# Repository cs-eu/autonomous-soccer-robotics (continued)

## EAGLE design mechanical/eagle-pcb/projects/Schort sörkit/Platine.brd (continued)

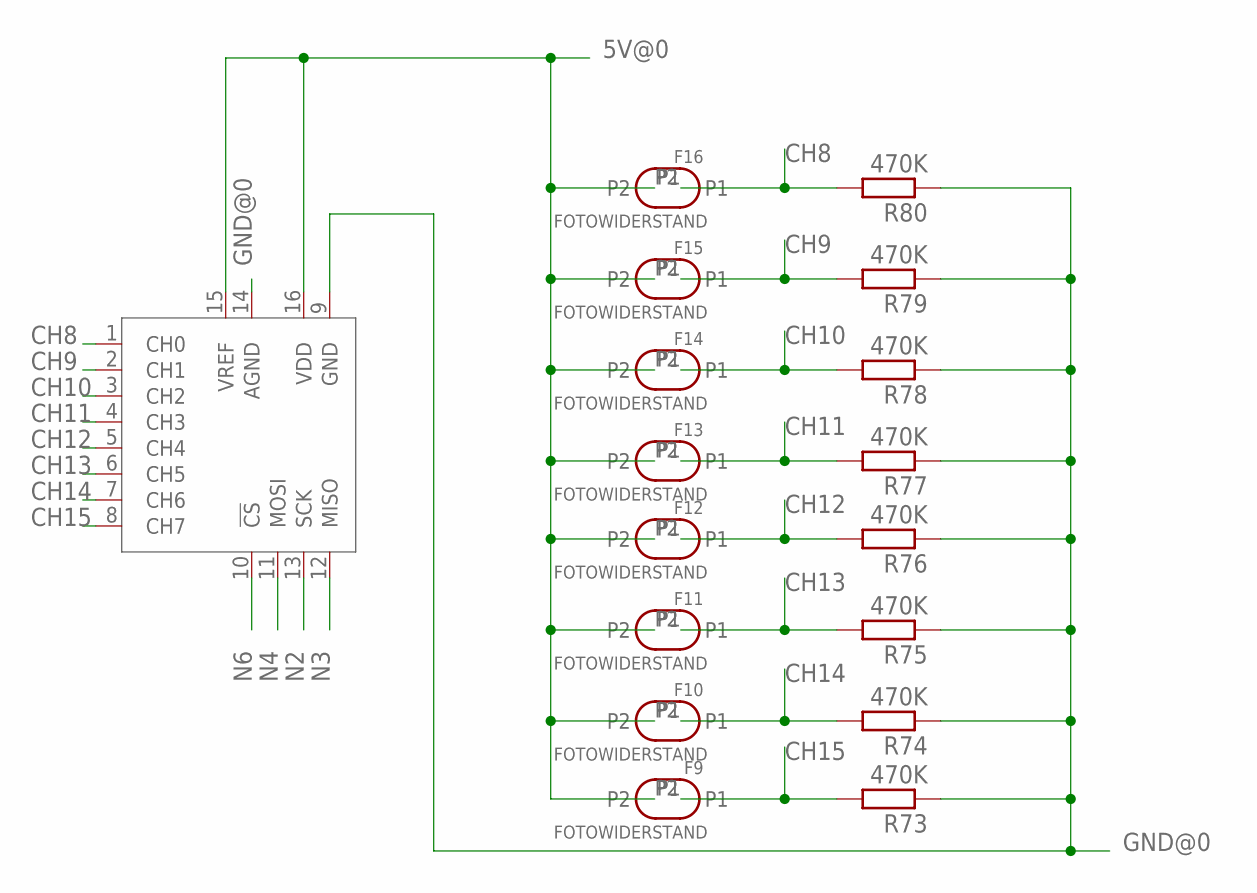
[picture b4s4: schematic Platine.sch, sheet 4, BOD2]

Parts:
F9, F10, F11, F12, F13, F14, F15, F16: FOTOWIDERSTAND
R73, R74, R75, R76, R77, R78, R79, R80: 470K; 0207/7
U$7: MCP3008P; DIL16

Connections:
5V@0: F9.P2, F10.P2, F11.P2, F12.P2, F13.P2, F14.P2, F15.P2, F16.P2, U$7.15 (VREF), U$7.16 (VDD); also elsewhere on the board
CH8: F16.P1, R80.2, U$7.1 (CH0)
CH9: F15.P1, R79.2, U$7.2 (CH1)
CH10: F14.P1, R78.2, U$7.3 (CH2)
CH11: F13.P1, R77.2, U$7.4 (CH3)
CH12: F12.P1, R76.2, U$7.5 (CH4)
CH13: F11.P1, R75.2, U$7.6 (CH5)
CH14: F10.P1, R74.2, U$7.7 (CH6)
CH15: F9.P1, R73.2, U$7.8 (CH7)
GND@0: R73.1, R74.1, R75.1, R76.1, R77.1, R78.1, R79.1, R80.1, U$7.9 (GND), U$7.14 (AGND); also elsewhere on the board
N2: U$7.13 (SCK); also elsewhere on the board
N3: U$7.12 (MISO); also elsewhere on the board
N4: U$7.11 (MOSI); also elsewhere on the board
N6: U$7.10 (!CS); also elsewhere on the board

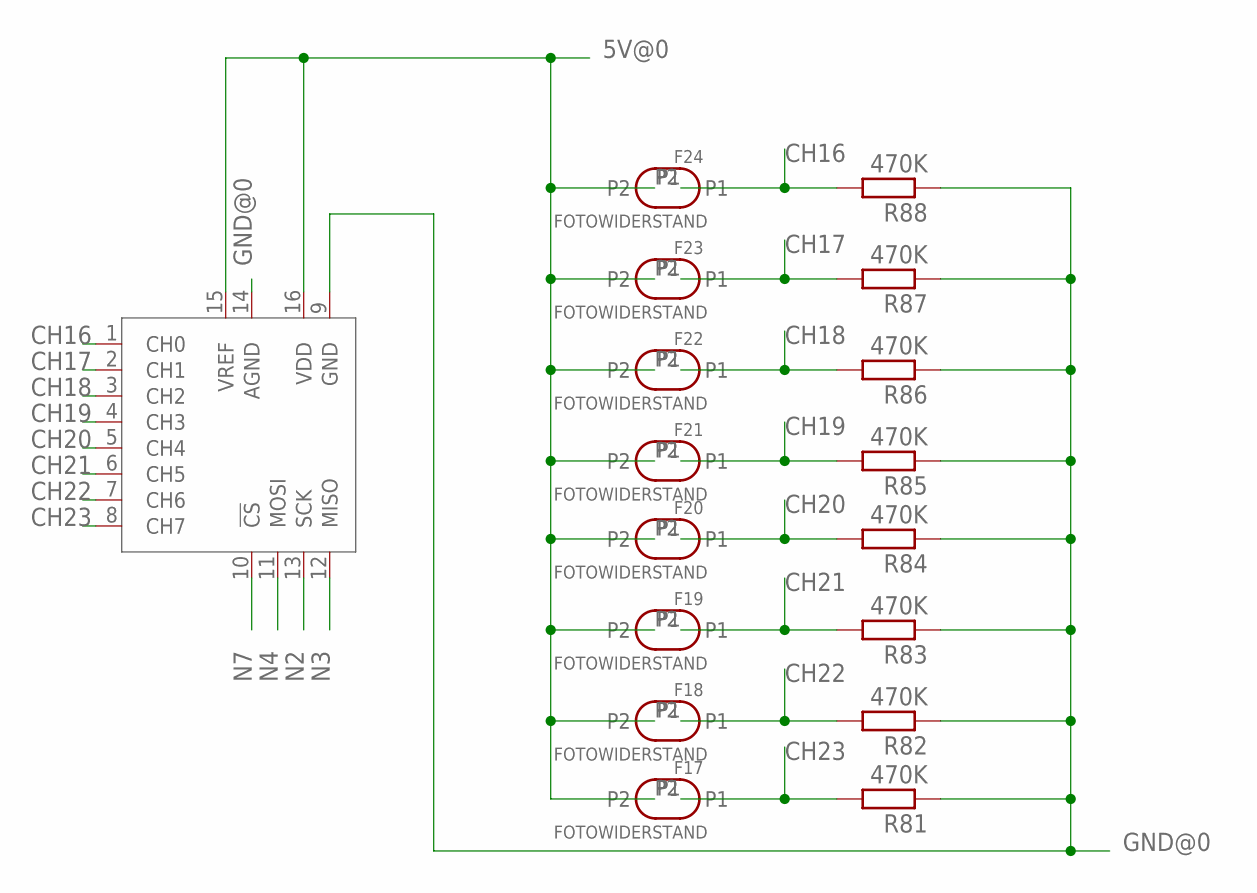
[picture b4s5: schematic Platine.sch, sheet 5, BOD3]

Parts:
F17, F18, F19, F20, F21, F22, F23, F24: FOTOWIDERSTAND
R81, R82, R83, R84, R85, R86, R87, R88: 470K; 0207/7
U$8: MCP3008P; DIL16

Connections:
5V@0: F17.P2, F18.P2, F19.P2, F20.P2, F21.P2, F22.P2, F23.P2, F24.P2, U$8.15 (VREF), U$8.16 (VDD); also elsewhere on the board
CH16: F24.P1, R88.2, U$8.1 (CH0)
CH17: F23.P1, R87.2, U$8.2 (CH1)
CH18: F22.P1, R86.2, U$8.3 (CH2)
CH19: F21.P1, R85.2, U$8.4 (CH3)
CH20: F20.P1, R84.2, U$8.5 (CH4)
CH21: F19.P1, R83.2, U$8.6 (CH5)
CH22: F18.P1, R82.2, U$8.7 (CH6)
CH23: F17.P1, R81.2, U$8.8 (CH7)
GND@0: R81.1, R82.1, R83.1, R84.1, R85.1, R86.1, R87.1, R88.1, U$8.9 (GND), U$8.14 (AGND); also elsewhere on the board
N2: U$8.13 (SCK); also elsewhere on the board
N3: U$8.12 (MISO); also elsewhere on the board
N4: U$8.11 (MOSI); also elsewhere on the board
N7: U$8.10 (!CS); also elsewhere on the board

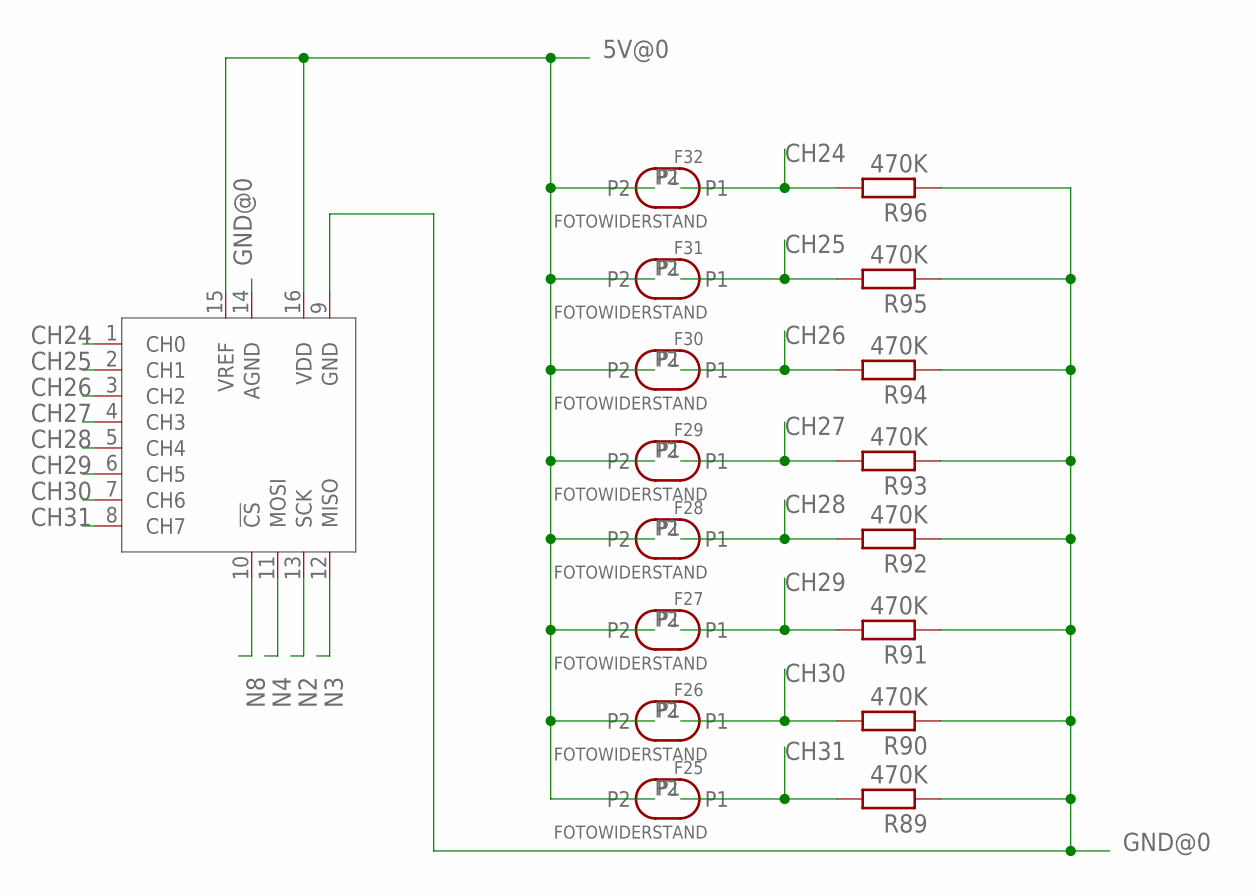
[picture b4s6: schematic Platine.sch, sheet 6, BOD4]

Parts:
F25, F26, F27, F28, F29, F30, F31, F32: FOTOWIDERSTAND
R89, R90, R91, R92, R93, R94, R95, R96: 470K; 0207/7
U$10: MCP3008P; DIL16

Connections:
5V@0: F25.P2, F26.P2, F27.P2, F28.P2, F29.P2, F30.P2, F31.P2, F32.P2, U$10.15 (VREF), U$10.16 (VDD); also elsewhere on the board
CH24: F32.P1, R96.2, U$10.1 (CH0)
CH25: F31.P1, R95.2, U$10.2 (CH1)
CH26: F30.P1, R94.2, U$10.3 (CH2)
CH27: F29.P1, R93.2, U$10.4 (CH3)
CH28: F28.P1, R92.2, U$10.5 (CH4)
CH29: F27.P1, R91.2, U$10.6 (CH5)
CH30: F26.P1, R90.2, U$10.7 (CH6)
CH31: F25.P1, R89.2, U$10.8 (CH7)
GND@0: R89.1, R90.1, R91.1, R92.1, R93.1, R94.1, R95.1, R96.1, U$10.9 (GND), U$10.14 (AGND); also elsewhere on the board
N2: U$10.13 (SCK); also elsewhere on the board
N3: U$10.12 (MISO); also elsewhere on the board
N4: U$10.11 (MOSI); also elsewhere on the board
N8: U$10.10 (!CS); also elsewhere on the board

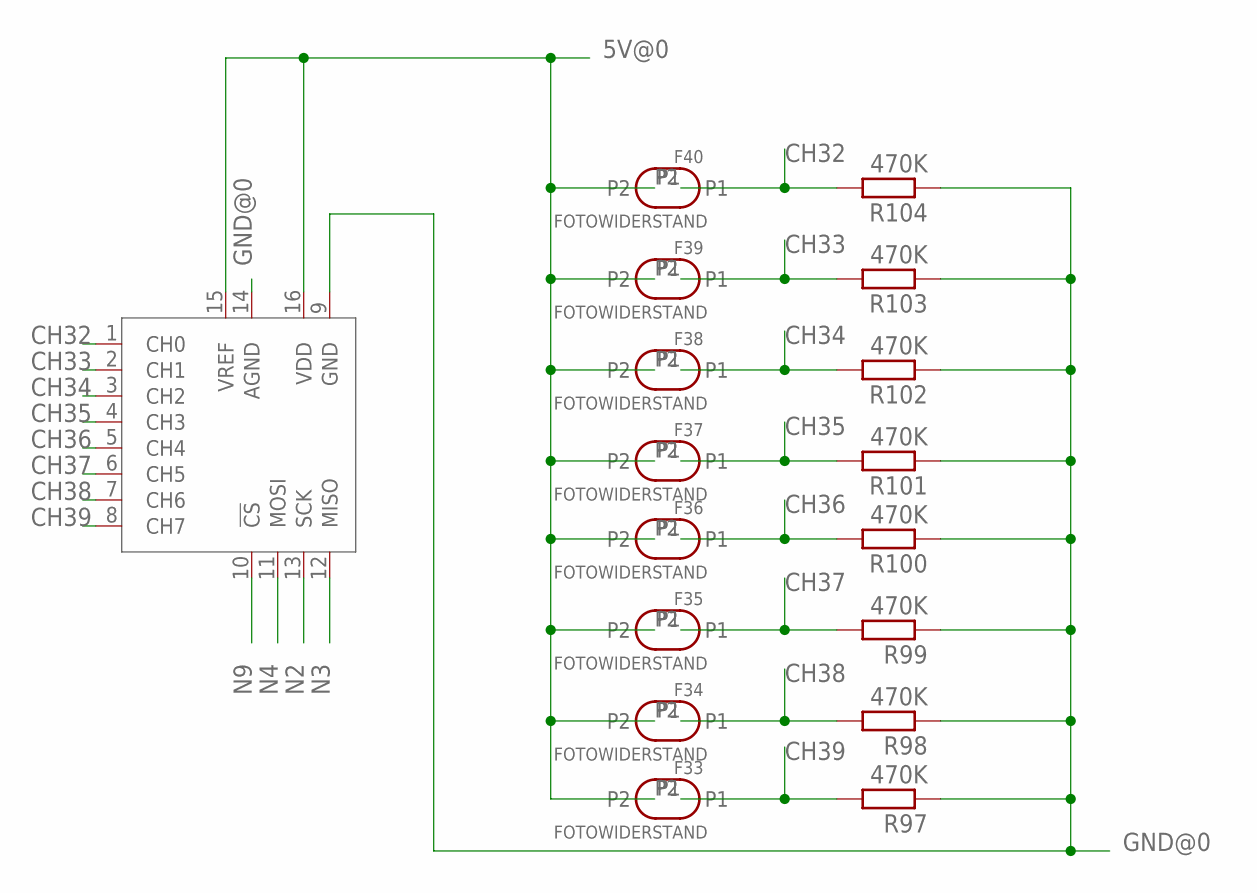
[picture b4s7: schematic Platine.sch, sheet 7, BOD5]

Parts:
F33, F34, F35, F36, F37, F38, F39, F40: FOTOWIDERSTAND
R97, R98, R99, R100, R101, R102, R103, R104: 470K; 0207/7
U$11: MCP3008P; DIL16

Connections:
5V@0: F33.P2, F34.P2, F35.P2, F36.P2, F37.P2, F38.P2, F39.P2, F40.P2, U$11.15 (VREF), U$11.16 (VDD); also elsewhere on the board
CH32: F40.P1, R104.2, U$11.1 (CH0)
CH33: F39.P1, R103.2, U$11.2 (CH1)
CH34: F38.P1, R102.2, U$11.3 (CH2)
CH35: F37.P1, R101.2, U$11.4 (CH3)
CH36: F36.P1, R100.2, U$11.5 (CH4)
CH37: F35.P1, R99.2, U$11.6 (CH5)
CH38: F34.P1, R98.2, U$11.7 (CH6)
CH39: F33.P1, R97.2, U$11.8 (CH7)
GND@0: R97.1, R98.1, R99.1, R100.1, R101.1, R102.1, R103.1, R104.1, U$11.9 (GND), U$11.14 (AGND); also elsewhere on the board
N2: U$11.13 (SCK); also elsewhere on the board
N3: U$11.12 (MISO); also elsewhere on the board
N4: U$11.11 (MOSI); also elsewhere on the board
N9: U$11.10 (!CS); also elsewhere on the board

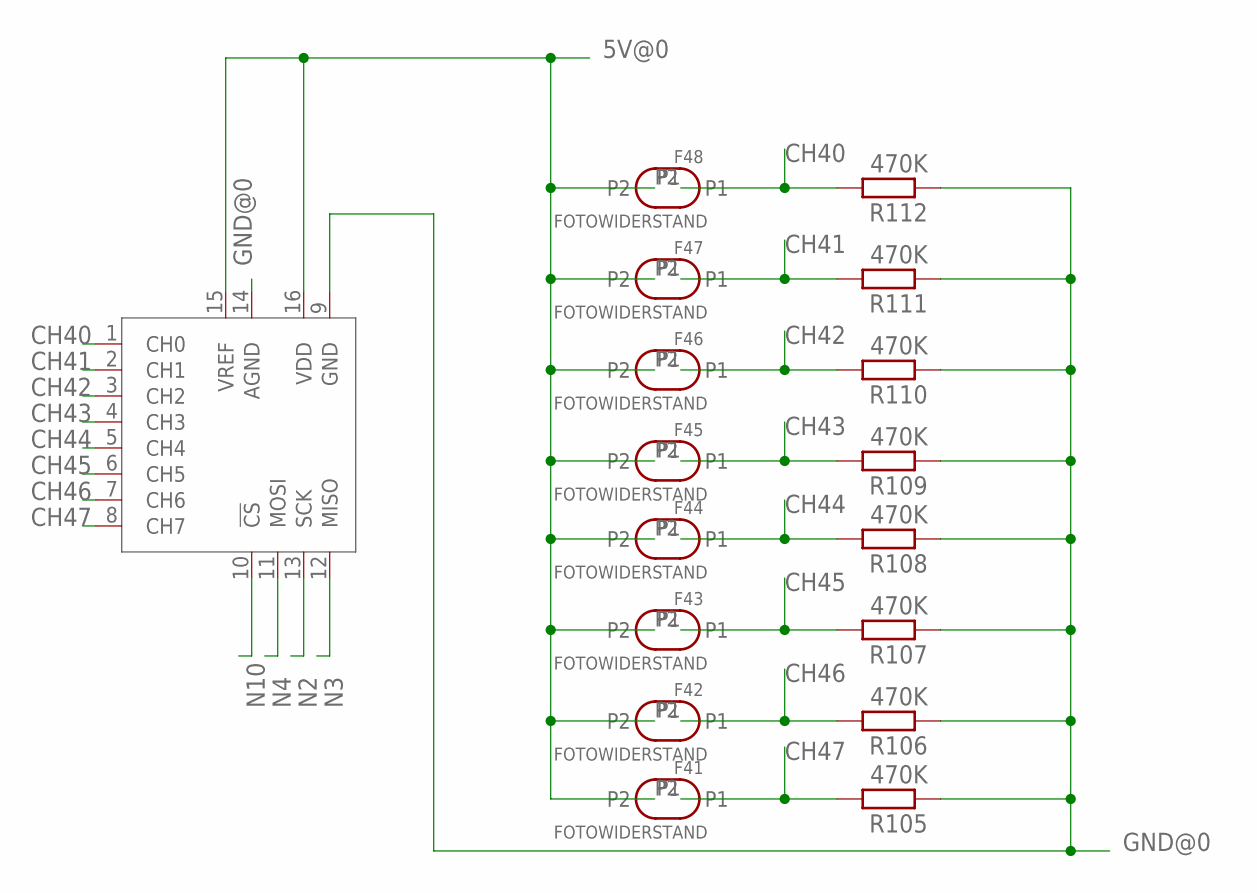
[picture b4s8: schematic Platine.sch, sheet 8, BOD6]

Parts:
F41, F42, F43, F44, F45, F46, F47, F48: FOTOWIDERSTAND
R105, R106, R107, R108, R109, R110, R111, R112: 470K; 0207/7
U$12: MCP3008P; DIL16

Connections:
5V@0: F41.P2, F42.P2, F43.P2, F44.P2, F45.P2, F46.P2, F47.P2, F48.P2, U$12.15 (VREF), U$12.16 (VDD); also elsewhere on the board
CH40: F48.P1, R112.2, U$12.1 (CH0)
CH41: F47.P1, R111.2, U$12.2 (CH1)
CH42: F46.P1, R110.2, U$12.3 (CH2)
CH43: F45.P1, R109.2, U$12.4 (CH3)
CH44: F44.P1, R108.2, U$12.5 (CH4)
CH45: F43.P1, R107.2, U$12.6 (CH5)
CH46: F42.P1, R106.2, U$12.7 (CH6)
CH47: F41.P1, R105.2, U$12.8 (CH7)
GND@0: R105.1, R106.1, R107.1, R108.1, R109.1, R110.1, R111.1, R112.1, U$12.9 (GND), U$12.14 (AGND); also elsewhere on the board
N2: U$12.13 (SCK); also elsewhere on the board
N3: U$12.12 (MISO); also elsewhere on the board
N4: U$12.11 (MOSI); also elsewhere on the board
N10: U$12.10 (!CS); also elsewhere on the board

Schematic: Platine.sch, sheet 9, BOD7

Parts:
F49, F50, F51, F52, F53, F54, F55, F56: FOTOWIDERSTAND
R113, R114, R115, R116, R117, R118, R119, R120: 470K; 0207/7
U$13: MCP3008P; DIL16

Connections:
5V@0: F49.P2, F50.P2, F51.P2, F52.P2, F53.P2, F54.P2, F55.P2, F56.P2, U$13.15 (VREF), U$13.16 (VDD); also elsewhere on the board
CH48: F56.P1, R120.2, U$13.1 (CH0)
CH49: F55.P1, R119.2, U$13.2 (CH1)
CH50: F54.P1, R118.2, U$13.3 (CH2)
CH51: F53.P1, R117.2, U$13.4 (CH3)
CH52: F52.P1, R116.2, U$13.5 (CH4)
CH53: F51.P1, R115.2, U$13.6 (CH5)
CH54: F50.P1, R114.2, U$13.7 (CH6)
CH55: F49.P1, R113.2, U$13.8 (CH7)
GND@0: R113.1, R114.1, R115.1, R116.1, R117.1, R118.1, R119.1, R120.1, U$13.9 (GND), U$13.14 (AGND); also elsewhere on the board
N2: U$13.13 (SCK); also elsewhere on the board
N3: U$13.12 (MISO); also elsewhere on the board
N4: U$13.11 (MOSI); also elsewhere on the board
N11: U$13.10 (!CS); also elsewhere on the board

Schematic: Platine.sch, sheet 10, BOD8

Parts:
F57, F58, F59, F60, F61, F62, F63, F64: FOTOWIDERSTAND
R121, R122, R123, R124, R125, R126, R127, R128: 470K; 0207/7
U$14: MCP3008P; DIL16

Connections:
5V@0: F57.P2, F58.P2, F59.P2, F60.P2, F61.P2, F62.P2, F63.P2, F64.P2, U$14.15 (VREF), U$14.16 (VDD); also elsewhere on the board
CH56: F64.P1, R128.2, U$14.1 (CH0)
CH57: F63.P1, R127.2, U$14.2 (CH1)
CH58: F62.P1, R126.2, U$14.3 (CH2)
CH59: F61.P1, R125.2, U$14.4 (CH3)
CH60: F60.P1, R124.2, U$14.5 (CH4)
CH61: F59.P1, R123.2, U$14.6 (CH5)
CH62: F58.P1, R122.2, U$14.7 (CH6)
CH63: F57.P1, R121.2, U$14.8 (CH7)
GND@0: R121.1, R122.1, R123.1, R124.1, R125.1, R126.1, R127.1, R128.1, U$14.9 (GND), U$14.14 (AGND); also elsewhere on the board
N2: U$14.13 (SCK); also elsewhere on the board
N3: U$14.12 (MISO); also elsewhere on the board
N4: U$14.11 (MOSI); also elsewhere on the board
N12: U$14.10 (!CS); also elsewhere on the board

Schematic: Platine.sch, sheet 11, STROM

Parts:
AKKU: TERMINAL
SH1, SH2, SH3, SH4: SHORT-HA5; SHORT_ALL-50
SPANNUNGSWANDLERAUSGANG: TERMINAL

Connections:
5VSPW: SPANNUNGSWANDLERAUSGANG.V+ (+V); also elsewhere on the board
12VAKKU: AKKU.V+ (+V), SH3.2, SH4.2; also elsewhere on the board
12VMOTOR: SH4.1; also elsewhere on the board
12VSCHUSS: SH3.1; also elsewhere on the board
GNDAKKU: AKKU.GND, SH1.1, SH2.1; also elsewhere on the board
GNDMOTOR: SH1.2; also elsewhere on the board
GNDSCHUSS: SH2.2; also elsewhere on the board
GNDSPW: SPANNUNGSWANDLERAUSGANG.GND; also elsewhere on the board

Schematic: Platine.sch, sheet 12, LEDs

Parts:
LED1, LED2, LED3, LED4, LED5, LED6, LED7, LED8, LED9, LED10, LED11, LED12, LED13, LED14, LED15, LED16, LED17, LED18, LED19, LED20, LED21, LED22, LED23, LED24, LED25, LED26, LED27, LED28, LED29, LED30, LED31, LED32, LED33, LED34, LED35, LED36, LED37, LED38, LED39, LED40, LED41, LED42, LED43, LED44, LED45, LED46, LED47, LED48, LED49, LED50, LED51, LED52, LED53, LED54, LED55, LED56, LED57, LED58, LED59, LED60, LED61, LED62, LED63, LED64: LEDLED3MM2; 3MM
RL1, RL2, RL3, RL4, RL5, RL6, RL7, RL8, RL9, RL10, RL11, RL12, RL13, RL14, RL15, RL16, RL17, RL18, RL19, RL20, RL21, RL22, RL23, RL24, RL25, RL26, RL27, RL28, RL29, RL30, RL31, RL32, RL33, RL34, RL35, RL36, RL37, RL38, RL39, RL40, RL41, RL42, RL43, RL44, RL45, RL46, RL47, RL48, RL49, RL50, RL51, RL52, RL53, RL54, RL55, RL56, RL57, RL58, RL59, RL60, RL61, RL62, RL63, RL64: 130; 0207/7

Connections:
5VSPW: RL1.1, RL2.1, RL3.1, RL4.1, RL5.1, RL6.1, RL7.1, RL8.1, RL9.1, RL10.1, RL11.1, RL12.1, RL13.1, RL14.1, RL15.1, RL16.1, RL17.1, RL18.1, RL19.1, RL20.1, RL21.1, RL22.1, RL23.1, RL24.1, RL25.1, RL26.1, RL27.1, RL28.1, RL29.1, RL30.1, RL31.1, RL32.1, RL33.1, RL34.1, RL35.1, RL36.1, RL37.1, RL38.1, RL39.1, RL40.1, RL41.1, RL42.1, RL43.1, RL44.1, RL45.1, RL46.1, RL47.1, RL48.1, RL49.1, RL50.1, RL51.1, RL52.1, RL53.1, RL54.1, RL55.1, RL56.1, RL57.1, RL58.1, RL59.1, RL60.1, RL61.1, RL62.1, RL63.1, RL64.1; also elsewhere on the board
GNDSPW: LED1.K (C), LED2.K (C), LED3.K (C), LED4.K (C), LED5.K (C), LED6.K (C), LED7.K (C), LED8.K (C), LED9.K (C), LED10.K (C), LED11.K (C), LED12.K (C), LED13.K (C), LED14.K (C), LED15.K (C), LED16.K (C), LED17.K (C), LED18.K (C), LED19.K (C), LED20.K (C), LED21.K (C), LED22.K (C), LED23.K (C), LED24.K (C), LED25.K (C), LED26.K (C), LED27.K (C), LED28.K (C), LED29.K (C), LED30.K (C), LED31.K (C), LED32.K (C), LED33.K (C), LED34.K (C), LED35.K (C), LED36.K (C), LED37.K (C), LED38.K (C), LED39.K (C), LED40.K (C), LED41.K (C), LED42.K (C), LED43.K (C), LED44.K (C), LED45.K (C), LED46.K (C), LED47.K (C), LED48.K (C), LED49.K (C), LED50.K (C), LED51.K (C), LED52.K (C), LED53.K (C), LED54.K (C), LED55.K (C), LED56.K (C), LED57.K (C), LED58.K (C), LED59.K (C), LED60.K (C), LED61.K (C), LED62.K (C), LED63.K (C), LED64.K (C); also elsewhere on the board
unnamed: LED4.A, RL4.2
unnamed: LED3.A, RL3.2
unnamed: LED2.A, RL2.2
unnamed: LED1.A, RL1.2
unnamed: LED8.A, RL8.2
unnamed: LED7.A, RL7.2
unnamed: LED6.A, RL6.2
unnamed: LED5.A, RL5.2
unnamed: LED12.A, RL12.2
unnamed: LED11.A, RL11.2
unnamed: LED10.A, RL10.2
unnamed: LED9.A, RL9.2
unnamed: LED16.A, RL16.2
unnamed: LED15.A, RL15.2
unnamed: LED14.A, RL14.2
unnamed: LED13.A, RL13.2
unnamed: LED20.A, RL20.2
unnamed: LED19.A, RL19.2
unnamed: LED18.A, RL18.2
unnamed: LED17.A, RL17.2
unnamed: LED24.A, RL24.2
unnamed: LED23.A, RL23.2
unnamed: LED22.A, RL22.2
unnamed: LED21.A, RL21.2
unnamed: LED28.A, RL28.2
unnamed: LED27.A, RL27.2
unnamed: LED26.A, RL26.2
unnamed: LED25.A, RL25.2
unnamed: LED32.A, RL32.2
unnamed: LED31.A, RL31.2
unnamed: LED30.A, RL30.2
unnamed: LED29.A, RL29.2
unnamed: LED36.A, RL36.2
unnamed: LED35.A, RL35.2
unnamed: LED34.A, RL34.2
unnamed: LED33.A, RL33.2
unnamed: LED40.A, RL40.2
unnamed: LED39.A, RL39.2
unnamed: LED38.A, RL38.2
unnamed: LED37.A, RL37.2
unnamed: LED44.A, RL44.2
unnamed: LED43.A, RL43.2
unnamed: LED42.A, RL42.2
unnamed: LED41.A, RL41.2
unnamed: LED48.A, RL48.2
unnamed: LED47.A, RL47.2
unnamed: LED46.A, RL46.2
unnamed: LED45.A, RL45.2
unnamed: LED52.A, RL52.2
unnamed: LED51.A, RL51.2
unnamed: LED50.A, RL50.2
unnamed: LED49.A, RL49.2
unnamed: LED56.A, RL56.2
unnamed: LED55.A, RL55.2
unnamed: LED54.A, RL54.2
unnamed: LED53.A, RL53.2
unnamed: LED60.A, RL60.2
unnamed: LED59.A, RL59.2
unnamed: LED58.A, RL58.2
unnamed: LED57.A, RL57.2
unnamed: LED64.A, RL64.2
unnamed: LED63.A, RL63.2
unnamed: LED62.A, RL62.2
unnamed: LED61.A, RL61.2

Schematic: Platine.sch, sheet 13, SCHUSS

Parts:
10A: FUSESH35; SH25
D1: 1N5404; DO201-15
Q1: IRF540; TO220
SCHUSS: TERMINAL

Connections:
7: Q1.1 (G); also elsewhere on the board
12VSCHUSS: 10A.1; also elsewhere on the board
GNDSCHUSS: Q1.3 (S); also elsewhere on the board
unnamed: D1.A, Q1.2 (D), SCHUSS.GND
unnamed: 10A.2, D1.C, SCHUSS.V+ (+V)

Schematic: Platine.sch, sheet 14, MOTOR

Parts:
MOTOREN1-2, MOTOREN3-4: MOTORTREIBER

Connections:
5V@2: MOTOREN1-2.VDD(5V), MOTOREN3-4.VDD(5V); also elsewhere on the board
12VMOTOR: MOTOREN1-2.VIN, MOTOREN3-4.VIN; also elsewhere on the board
28: MOTOREN1-2.M1FB; also elsewhere on the board
29: MOTOREN1-2.M1SF; also elsewhere on the board
30: MOTOREN1-2.M2FB; also elsewhere on the board
31: MOTOREN1-2.M2SF; also elsewhere on the board
32: MOTOREN3-4.M1FB; also elsewhere on the board
33: MOTOREN3-4.M1SF; also elsewhere on the board
34: MOTOREN3-4.M2FB; also elsewhere on the board
35: MOTOREN3-4.M2SF; also elsewhere on the board
36: MOTOREN1-2.M1IN1; also elsewhere on the board
37: MOTOREN1-2.M1IN2; also elsewhere on the board
38: MOTOREN1-2.M2IN1; also elsewhere on the board
39: MOTOREN1-2.M2IN2; also elsewhere on the board
40: MOTOREN3-4.M1IN1; also elsewhere on the board
41: MOTOREN3-4.M1IN2; also elsewhere on the board
42: MOTOREN3-4.M2IN1; also elsewhere on the board
43: MOTOREN3-4.M2IN2; also elsewhere on the board
44: MOTOREN1-2.M1PWM2; also elsewhere on the board
45: MOTOREN1-2.M2PWM2; also elsewhere on the board
46: MOTOREN3-4.M1PWM2; also elsewhere on the board
47: MOTOREN3-4.M2PWM2; also elsewhere on the board
GND@2: MOTOREN1-2.GND(5V), MOTOREN3-4.GND(5V); also elsewhere on the board
GNDMOTOR: MOTOREN1-2.GND, MOTOREN3-4.GND; also elsewhere on the board

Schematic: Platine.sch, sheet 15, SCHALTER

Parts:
SWITCH1, SWITCH2, SWITCH3, SWITCH4: KIPPY

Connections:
10: SWITCH1.VOUT1; also elsewhere on the board
11: SWITCH2.VOUT1; also elsewhere on the board
12: SWITCH3.VOUT1; also elsewhere on the board
13: SWITCH4.VOUT1; also elsewhere on the board
GND@2: SWITCH1.VIN, SWITCH2.VIN, SWITCH3.VIN, SWITCH4.VIN; also elsewhere on the board

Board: 4 copper layers, 287 parts (128 on the bottom side), 188 nets, no tracks yet.

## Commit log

2025-11-02 project structuring and cleanup
2025-11-02 Add MIT License to the project
